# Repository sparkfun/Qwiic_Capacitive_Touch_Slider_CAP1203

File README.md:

SparkFun Capacitive Touch Slider - CAP1203 (Qwiic)
========================================

[*SparkFun Capacitive Touch Slider - CAP1203 (Qwiic) (SEN-15344)*](https://www.sparkfun.com/products/15344)

An I2C based capacitive touch slider with 3 unique touch inputs.

Repository Contents
-------------------
* **/Hardware** - Eagle design files (.brd, .sch)

Documentation
--------------
* **[Arduino Library](https://github.com/sparkfun/Qwiic_Capacitive_Touch_Slider_Arduino_Library)** - Arduino library for the SparkFun Capacitive Touch Slider.
* **[Hookup Guide](https://learn.sparkfun.com/tutorials/capacitive-touch-slider-cap1203-hookup-guide)** - Basic hookup guide for the SparkFun Capacitive Touch Slider.

Product Versions
----------------
* [SparkFun Capacitive Touch Slider - CAP1203 (Qwiic) (SEN-15344)](https://www.sparkfun.com/products/15344) - Storefront Product

License Information
-------------------

This product is _**open source**_! 

Please review the LICENSE.md file for license information. 

If you have any questions or concerns on licensing, please contact technical support on our [SparkFun forums](https://forum.sparkfun.com/viewforum.php?f=152).

Distributed as-is; no warranty is given.

- Your friends at SparkFun.

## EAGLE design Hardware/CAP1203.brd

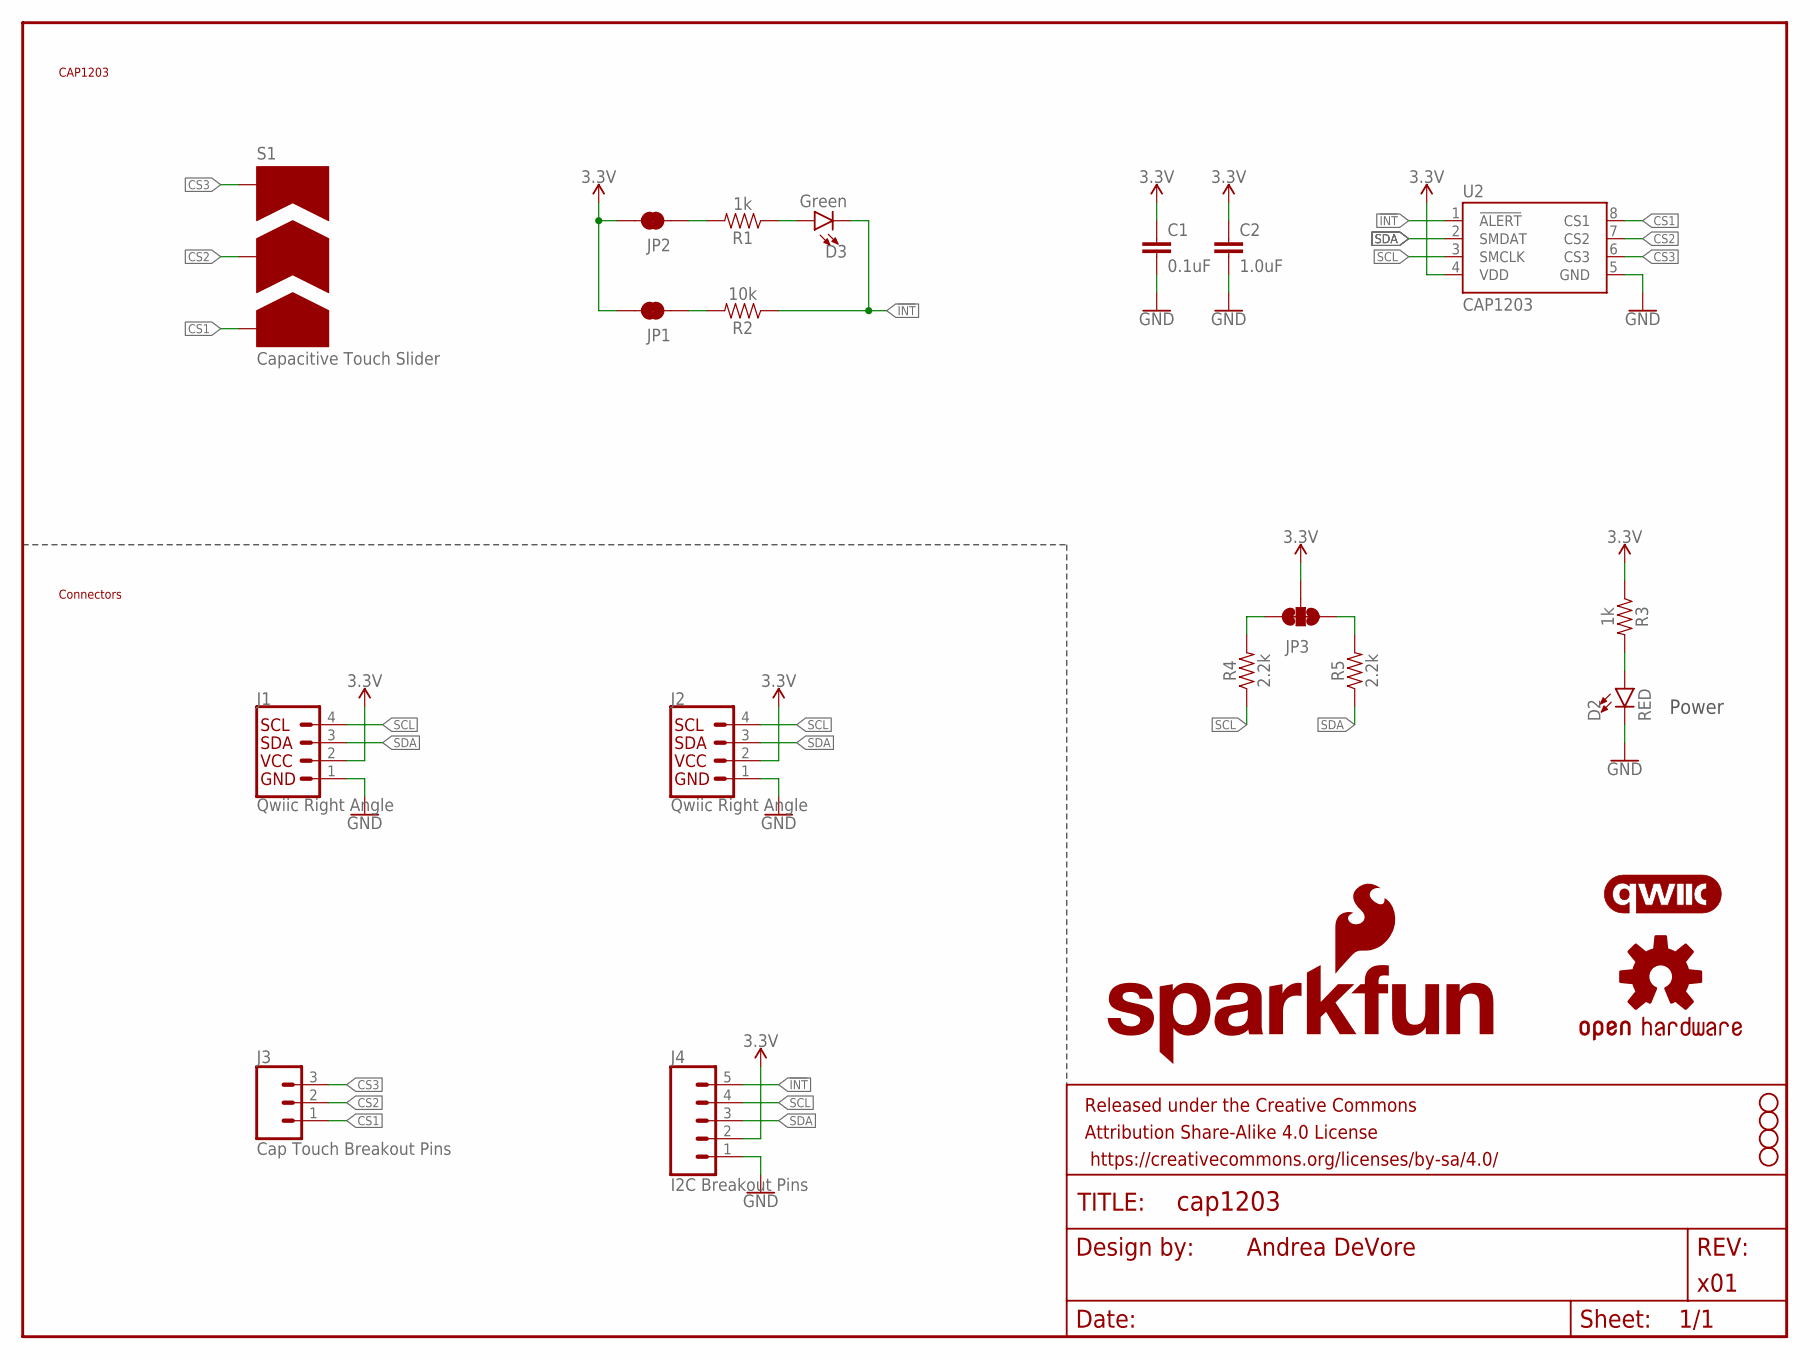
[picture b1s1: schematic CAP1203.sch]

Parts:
C1: 0.1uF; 0603
C2: 1.0uF; 0603
D2: RED; LED-0603
D3: Green; LED-1206-BOTTOM
FRAME1: FRAME-LETTER; CREATIVE_COMMONS
H1, H2, H3, H5: STAND-OFF
J1, J2: Qwiic Right Angle; JST04_1MM_RA
J3: Cap Touch Breakout Pins; 1X03_NO_SILK
J4: I2C Breakout Pins; 1X05_NO_SILK
JP1, JP2: JUMPER-SMT_2_NC_TRACE_SILK; SMT-JUMPER_2_NC_TRACE_SILK
JP3: JUMPER-SMT_3_2-NC_TRACE_SILK; SMT-JUMPER_3_2-NC_TRACE_SILK
LOGO1: SFE_LOGO_NAME_FLAME.1_INCH; SFE_LOGO_NAME_FLAME_.1
LOGO3: OSHW-LOGOS; OSHW-LOGO-S
R1, R3: 1k; 0603
R2: 10k; 0603
R4, R5: 2.2k; 0603
S1: CAP_SENSE_SLIDER
U2: CAP1203; SO08-TIGHT
U$17: QWIIC_LOGO_5MM; QWIIC_5MM

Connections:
3.3V: C1.1, C2.1, J1.2, J2.2, J4.2, JP1.2, JP2.2, JP3.2, R3.1, U2.4 (VDD)
!INT: D3.C, J4.5, R2.1, U2.1 (!ALERT)
CS1: J3.1, S1.1, U2.8 (CS1)
CS2: J3.2, S1.2, U2.7 (CS2)
CS3: J3.3, S1.3, U2.6 (CS3)
GND: C1.2, C2.2, D2.C, J1.1, J2.1, J4.1, U2.5 (GND)
unnamed: JP1.1, R2.2
unnamed: D2.A, R3.2
unnamed: JP2.1, R1.2
unnamed: JP3.3, R4.2
unnamed: JP3.1, R5.2
unnamed: D3.A, R1.1
SCL: J1.4, J2.4, J4.4, R4.1, U2.3 (SMCLK)
SDA: J1.3, J2.3, J4.3, R5.1, U2.2 (SMDAT)

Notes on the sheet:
Andrea DeVore
Power
Connectors
CAP1203
x01
Capacitive Touch Slider

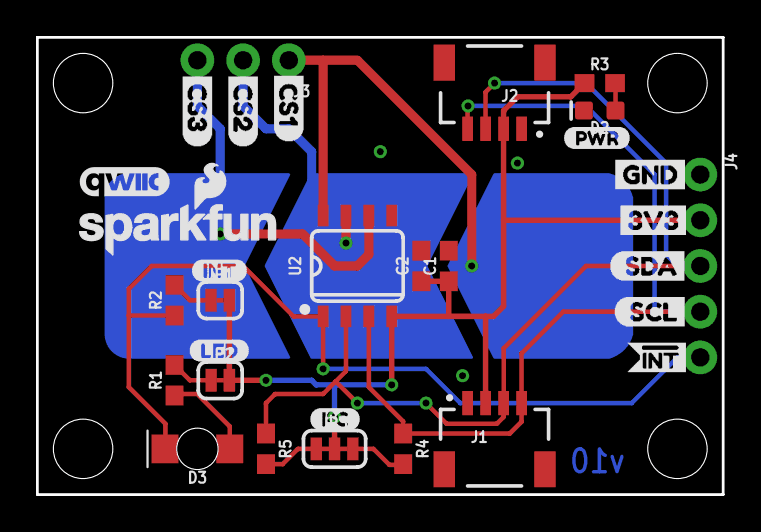
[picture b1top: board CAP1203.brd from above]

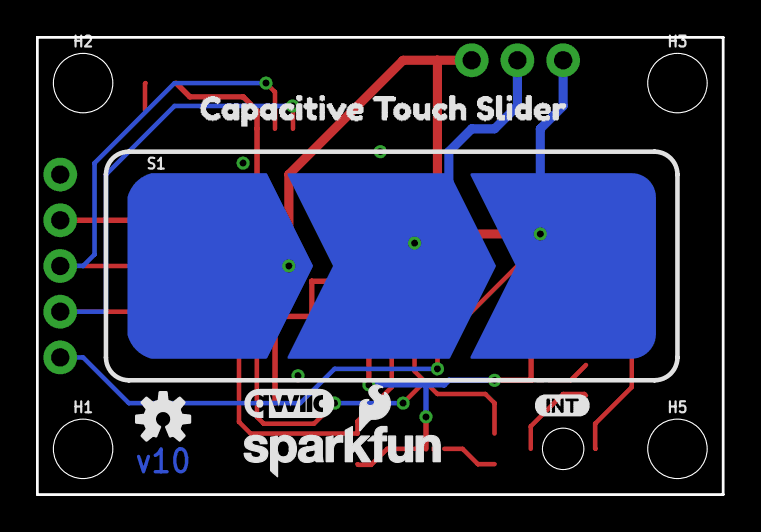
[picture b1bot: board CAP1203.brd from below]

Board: 2 copper layers, 38.1 x 25.4 mm, 42 parts (10 on the bottom side), 14 nets.

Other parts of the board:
LOGO2: SFE_LOGO_NAME_FLAME.1_INCH; SFE_LOGO_NAME_FLAME_.1
U$1: 3V3-04
U$2: GND-04
U$4: QWIIC_LOGO_5MM; QWIIC_5MM
U$5, U$14: INT0
U$7: #INT5
U$8: SCL3
U$9: SDA4
U$10: CS10
U$11: CS21
U$12: CS32
U$13: I_SUPER2_C-()-03
U$15: PWR-()-03
U$16: LED0
U$18: CAPACITIVE_TOUCH_SLIDER0

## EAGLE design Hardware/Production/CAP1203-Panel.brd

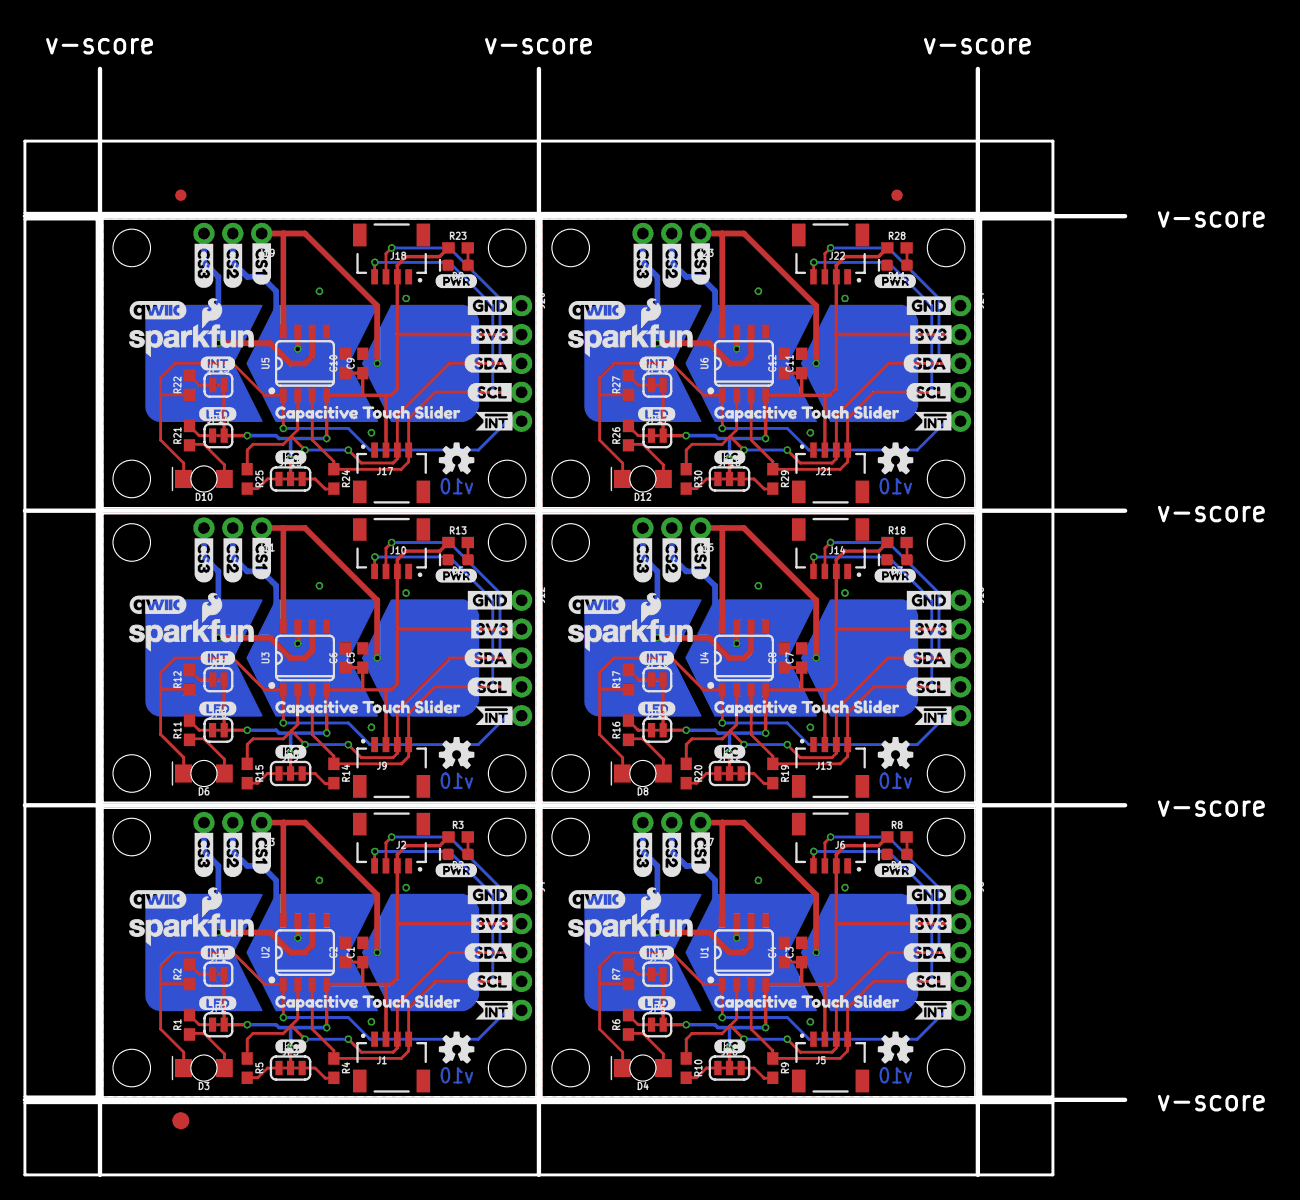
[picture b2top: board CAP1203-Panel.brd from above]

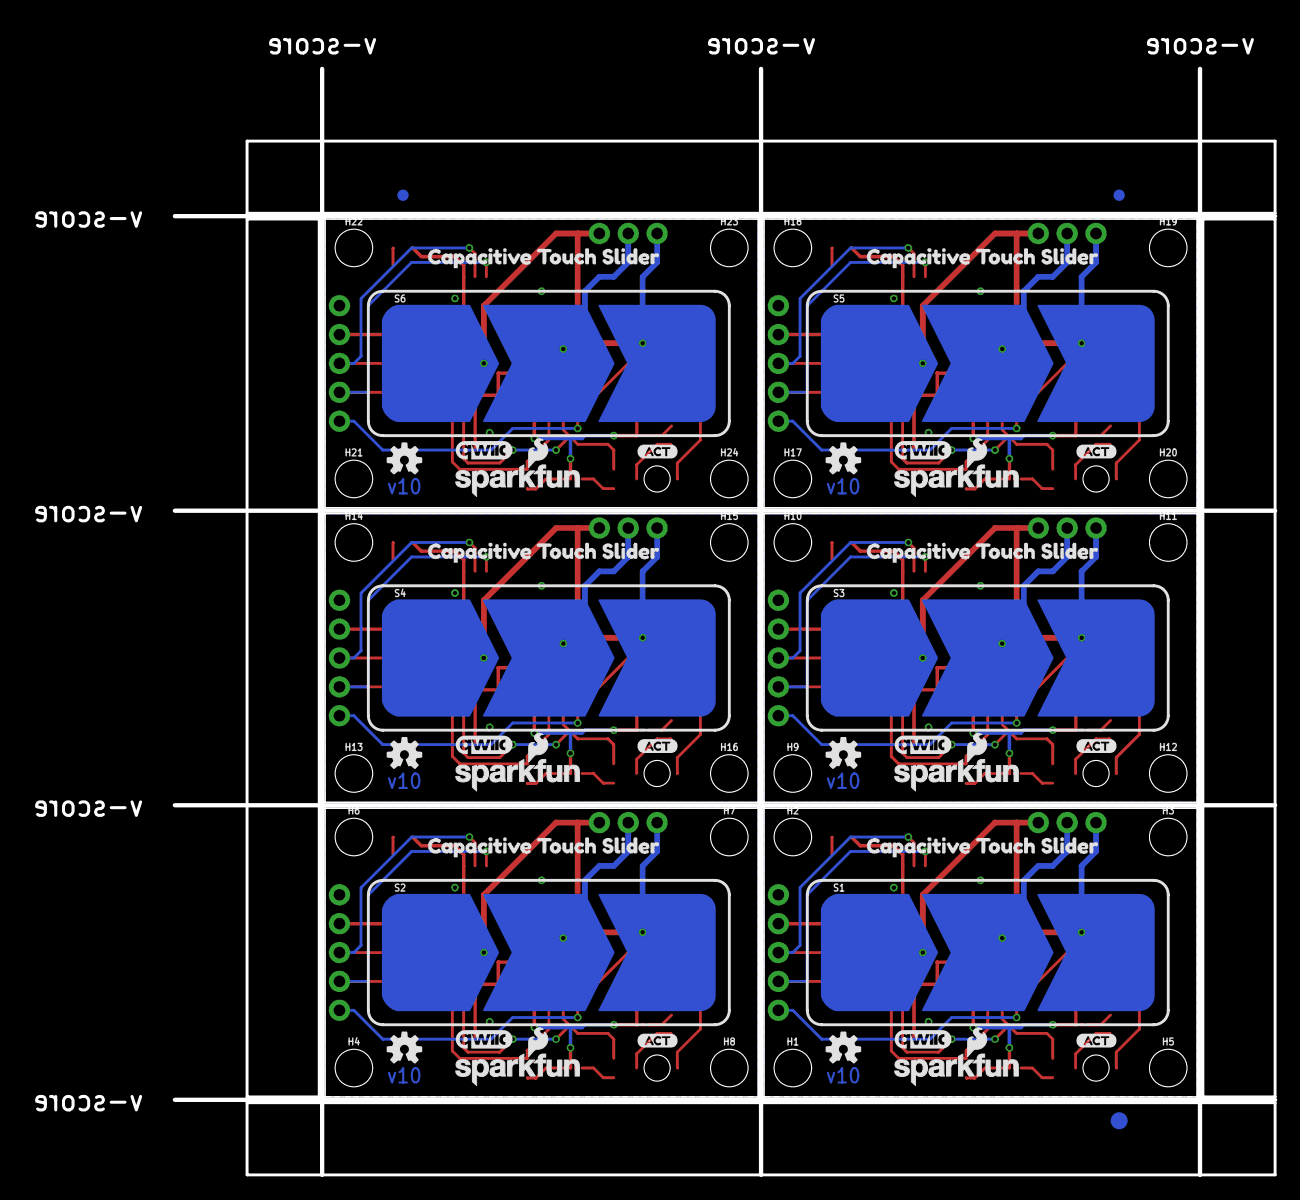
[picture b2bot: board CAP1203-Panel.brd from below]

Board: 2 copper layers, 110.0 x 101.2 mm, 264 parts (63 on the bottom side), 84 nets.

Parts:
C1, C3, C5, C7, C9, C11: 0.1uF; 0603
C2, C4, C6, C8, C10, C12: 1.0uF; 0603
D1, D2, D5, D7, D9, D11: RED; LED-0603
D3, D4, D6, D8, D10, D12: Green; LED-1206-BOTTOM
E$1, E$2, E$3, E$4: FIDUCIAL-1X2
E$5, E$6: FIDUCIAL-1.5X3
H1, H2, H3, H4, H5, H6, H7, H8, H9, H10, H11, H12, H13, H14, H15, H16, H17, H18, H19, H20, H21, H22, H23, H24: STAND-OFF
J1, J2, J5, J6, J9, J10, J13, J14, J17, J18, J21, J22: Qwiic Right Angle; JST04_1MM_RA
J3, J7, J11, J15, J19, J23: Cap Touch Breakout Pins; 1X03_NO_SILK
J4, J8, J12, J16, J20, J24: I2C Breakout Pins; 1X05_NO_SILK
JP1, JP2, JP4, JP5, JP7, JP8, JP10, JP11, JP13, JP14, JP16, JP17: JUMPER-SMT_2_NC_TRACE_SILK; SMT-JUMPER_2_NC_TRACE_SILK
JP3, JP6, JP9, JP12, JP15, JP18: JUMPER-SMT_3_2-NC_TRACE_SILK; SMT-JUMPER_3_2-NC_TRACE_SILK
LOGO1, LOGO2, LOGO4, LOGO8, LOGO9, LOGO12, LOGO13, LOGO16, LOGO17, LOGO20, LOGO21, LOGO24: SFE_LOGO_NAME_FLAME.1_INCH; SFE_LOGO_NAME_FLAME_.1
LOGO3, LOGO5, LOGO6, LOGO7, LOGO10, LOGO11, LOGO14, LOGO15, LOGO18, LOGO19, LOGO22, LOGO23: OSHW-LOGOS; OSHW-LOGO-S
R1, R3, R6, R8, R11, R13, R16, R18, R21, R23, R26, R28: 1k; 0603
R2, R7, R12, R17, R22, R27: 10k; 0603
R4, R5, R9, R10, R14, R15, R19, R20, R24, R25, R29, R30: 2.2k; 0603
S1, S2, S3, S4, S5, S6: CAP_SENSE_SLIDER
U1, U2, U3, U4, U5, U6: CAP1203; SO08-TIGHT
U$1, U$3, U$35, U$52, U$69, U$86: 3V3-04
U$2, U$5, U$36, U$53, U$70, U$87: GND-04
U$4, U$17, U$30, U$31, U$47, U$48, U$64, U$65, U$81, U$82, U$98, U$99: QWIIC_LOGO_5MM; QWIIC_5MM
U$6, U$32, U$49, U$66, U$83, U$100: ACT0
U$7, U$20, U$37, U$54, U$71, U$88: #INT5
U$8, U$21, U$38, U$55, U$72, U$89: SCL3
U$9, U$22, U$39, U$56, U$73, U$90: SDA4
U$10, U$23, U$40, U$57, U$74, U$91: CS10
U$11, U$24, U$41, U$58, U$75, U$92: CS21
U$12, U$25, U$42, U$59, U$76, U$93: CS32
U$13, U$27, U$44, U$61, U$78, U$95: I_SUPER2_C-()-03
U$14, U$28, U$45, U$62, U$79, U$96: INT0
U$15, U$29, U$46, U$63, U$80, U$97: PWR-()-03
U$16, U$26, U$43, U$60, U$77, U$94: LED0
U$18, U$19, U$33, U$34, U$50, U$51, U$67, U$68, U$84, U$85, U$101, U$102: CAPACITIVE_TOUCH_SLIDER0

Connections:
3.3V: C1.1, C2.1, J1.2, J2.2, J4.2, JP1.2, JP2.2, JP3.2, R3.1, U2.4
3.3V1: C3.1, C4.1, J5.2, J6.2, J8.2, JP4.2, JP5.2, JP6.2, R8.1, U1.4
3.3V2: C5.1, C6.1, J9.2, J10.2, J12.2, JP7.2, JP8.2, JP9.2, R13.1, U3.4
3.3V3: C7.1, C8.1, J13.2, J14.2, J16.2, JP10.2, JP11.2, JP12.2, R18.1, U4.4
3.3V4: C9.1, C10.1, J17.2, J18.2, J20.2, JP13.2, JP14.2, JP15.2, R23.1, U5.4
3.3V5: C11.1, C12.1, J21.2, J22.2, J24.2, JP16.2, JP17.2, JP18.2, R28.1, U6.4
!INT: D3.C, J4.5, R2.1, U2.1
!INT1: D4.C, J8.5, R7.1, U1.1
!INT2: D6.C, J12.5, R12.1, U3.1
!INT3: D8.C, J16.5, R17.1, U4.1
!INT4: D10.C, J20.5, R22.1, U5.1
!INT5: D12.C, J24.5, R27.1, U6.1
CS1: J3.1, S1.1, U2.8
CS2: J3.2, S1.2, U2.7
CS3: J3.3, S1.3, U2.6
CS4: J7.1, S2.1, U1.8
CS5: J7.2, S2.2, U1.7
CS6: J7.3, S2.3, U1.6
CS7: J11.1, S3.1, U3.8
CS8: J11.2, S3.2, U3.7
CS9: J11.3, S3.3, U3.6
CS10: J15.1, S4.1, U4.8
CS11: J15.2, S4.2, U4.7
CS12: J15.3, S4.3, U4.6
CS13: J19.1, S5.1, U5.8
CS14: J19.2, S5.2, U5.7
CS15: J19.3, S5.3, U5.6
CS16: J23.1, S6.1, U6.8
CS17: J23.2, S6.2, U6.7
CS18: J23.3, S6.3, U6.6
GND: C1.2, C2.2, D2.C, J1.1, J2.1, J4.1, U2.5
GND1: C3.2, C4.2, D1.C, J5.1, J6.1, J8.1, U1.5
GND2: C5.2, C6.2, D5.C, J9.1, J10.1, J12.1, U3.5
GND3: C7.2, C8.2, D7.C, J13.1, J14.1, J16.1, U4.5
GND4: C9.2, C10.2, D9.C, J17.1, J18.1, J20.1, U5.5
GND5: C11.2, C12.2, D11.C, J21.1, J22.1, J24.1, U6.5
unnamed: JP1.1, R2.2
unnamed: D2.A, R3.2
unnamed: JP2.1, R1.2
unnamed: JP3.3, R4.2
unnamed: JP3.1, R5.2
unnamed: D3.A, R1.1
unnamed: JP4.1, R7.2
unnamed: JP5.1, R6.2
unnamed: D4.A, R6.1
unnamed: D1.A, R8.2
unnamed: JP6.3, R9.2
unnamed: JP6.1, R10.2
unnamed: JP7.1, R12.2
unnamed: JP8.1, R11.2
unnamed: D6.A, R11.1
unnamed: D5.A, R13.2
unnamed: JP9.3, R14.2
unnamed: JP9.1, R15.2
unnamed: JP10.1, R17.2
unnamed: JP11.1, R16.2
unnamed: D8.A, R16.1
unnamed: D7.A, R18.2
unnamed: JP12.3, R19.2
unnamed: JP12.1, R20.2
unnamed: JP13.1, R22.2
unnamed: JP14.1, R21.2
unnamed: D10.A, R21.1
unnamed: D9.A, R23.2
unnamed: JP15.3, R24.2
unnamed: JP15.1, R25.2
unnamed: JP16.1, R27.2
unnamed: JP17.1, R26.2
unnamed: D12.A, R26.1
unnamed: D11.A, R28.2
unnamed: JP18.3, R29.2
unnamed: JP18.1, R30.2
SCL: J1.4, J2.4, J4.4, R4.1, U2.3
SCL1: J5.4, J6.4, J8.4, R9.1, U1.3
SCL2: J9.4, J10.4, J12.4, R14.1, U3.3
SCL3: J13.4, J14.4, J16.4, R19.1, U4.3
SCL4: J17.4, J18.4, J20.4, R24.1, U5.3
SCL5: J21.4, J22.4, J24.4, R29.1, U6.3
SDA: J1.3, J2.3, J4.3, R5.1, U2.2
SDA1: J5.3, J6.3, J8.3, R10.1, U1.2
SDA2: J9.3, J10.3, J12.3, R15.1, U3.2
SDA3: J13.3, J14.3, J16.3, R20.1, U4.2
SDA4: J17.3, J18.3, J20.3, R25.1, U5.2
SDA5: J21.3, J22.3, J24.3, R30.1, U6.2

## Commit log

2019-03-25 Initial commit of Capacitive Touch Slider board design
2019-03-26 Design review revisions
    * Updated brd and sch to match SparkFun design standards
    * Updated symbol to depict slider
    * Updated silkscreen text
2019-03-27 Panelized board
    * Ran panelization script for production
    * Added PROD_ID to CAP1203 sensor
2019-03-27 Added CAP1203 from SparkFun library
    * Replaced current CAP1203 with SparkFun library version
    * Updated in both sch and brd files
2019-04-17 Updated CAP1203 for production
    * Moved PTH for capactive touch
    * Updated traces accordingly
    * Enlarged and moved labels
2019-04-18 Removed extraneous files
2019-04-18 Removed wire stub
2019-04-18 Removed wire stub (correct now)
2019-04-19 Fixed border
2019-04-19 Fixed silkscreen and labels
2019-05-24 Updated hookup guide link
    Name of the tutorial changed, which changed the link address

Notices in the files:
parts and their libraries:
SparkFun-Aesthetics: Licensing: Creative Commons ShareAlike 4.0 International - https://creativecommons.org/licenses/by-sa/4.0
SparkFun-Aesthetics: Released under the Creative Commons Attribution Share-Alike 4.0 License
SparkFun-Aesthetics: https://creativecommons.org/licenses/by-sa/4.0
